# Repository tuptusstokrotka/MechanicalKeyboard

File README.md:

# PlusMinus 40

Inspired by [Mochi40](https://github.com/Aidan-OS/Mochi40), which already allows you to choose 1 out of 4 bottom row layout, but this wasn't enough for me. This is my first approach to 40% keyboards and with a changed bottom row to make it fit to my needs I gave it a go.

So I made this:

[Keyboard Layout Editor](http://www.keyboard-layout-editor.com/##@_name=PlusMinus%2040&author=Julian%3B&@_c=%23aaaaaa%20%3B&=0,0&_c=%23cccccc%20%3B&=0,1&=0,2&=0,3&=0,4&=0,5&=4,5&=4,4&=4,3&=4,2&=4,1&_c=%23777777%20&w:1.5%3B&=4,0%3B&@_w:1.25%3B&=1,0&_c=%23cccccc%20%3B&=1,1&=1,2&=1,3&=1,4&=1,5&=5,5&=5,4&=5,3&=5,2&=5,1&_c=%23aaaaaa%20&w:1.25%3B&=5,0%3B&@_c=%23777777%20&w:1.5%3B&=2,0&_c=%23cccccc%20%3B&=2,1&=2,2&=2,3&=2,4&=2,5&=6,5&=6,4&=6,3&=6,2&=6,1&=6,0%3B&@_y:-0.5&x:12.75&c=%23aaaaaa%20%3B&=7,0%0A%0A%0A%0A%0A%0A%0A%0A%0Ae0%3B&@_y:-0.5&c=%23777777%20&w:1.25%3B&=3,0&_w:1.25%3B&=3,1&_w:1.25%3B&=3,2&_c=%23aaaaaa%20&w:2.25%3B&=3,4&_w:2.75%3B&=7,5&_c=%23777777%20&w:1.25%3B&=7,3&_w:1.25%3B&=7,2&_w:1.25%3B&=7,1)

The files needed for https://jlcpcb.com are located in the production folder:

* `pcb/production`

Once `pcb.zip` has been uploaded, you can continue with the selected default options. You can optionally change the solder mask color, which changes the final color of your PCB.

When using their assembly service, you will need to upload the following files separately:

* `bom.csv`
* `positions.csv`

These files were all generated with Fabrication Toolkit for KiCad: https://github.com/bennymeg/Fabrication-Toolkit

## Acrylic Case

Case files are in the `DXF` folder.

#### note It is nessessary to add at least 2 stanoffs in the middle of a keyboard, due to the bending
---

### Parts List
| Description | Qty | Notes |
| ----------- | --- | ----- |
| 3mm acrylic | 7 | Qty = number of case layers
| 1.5mm acrylic | 1 | Switch plate
| M3x20mm chicago bolt | 6 | [Link](https://www.aliexpress.us/item/2251832451307213.html)
| M3x10mm chicago bolt | 1 | [Link](https://www.aliexpress.us/item/2251832451307213.html)
| M3x6mm screw | 1 - 6 | [Link](https://www.aliexpress.us/item/2255800885711092.html)
| M2x4mm round standoff | 7 | [Link](https://www.aliexpress.us/item/2251832782591461.html)
| M2x3mm screw | 7 | [Link](https://www.aliexpress.us/item/2255800480170108.html)
| M2x4mm screw | 7 | [Link](https://www.aliexpress.us/item/2255800480170108.html)
| 1mm EVA foam | 1 | Case foam
| 1.5mm EVA foam | 1 | Switch plate foam, [link](https://www.aliexpress.us/item/3256804208838525.html)
| 2mm EVA foam | 1 | Switch plate foam
| MX Switch | 38 - 44 |
| Adhesive rubber feet | 4

Keycap sizes will depend on the layout you're building (refer to KLE layout above).  Blank uniform-profile keycaps works really great for this keyboard since the keys have a vertical orientation.  I found my blank XDA PBT keycaps on AliExpress.  The specific ones I use in my build were purchased [here (1u - 2u)](https://www.aliexpress.us/item/3256804203440964.html) and [here (3u)](https://www.aliexpress.us/item/3256801190573750.html).

| Keycap | Qty |
| ------ | --- |
| 1u | 18 - 28
| 1.25u | 8
| 1.5u | 4
| 1.75u | 4
| 2u | 0 - 4
| 3u | 0 - 2

### Assembly

The M3 hardware is for the keyboard case.  The shorter M3 fastener goes above the USB connector.  You will need to use a wafer head (flat) screw on the bottom to keep the port clear for the USB cable.  You can optionally use the same M3x6mm wafer head screws for the entire bottom of the case instad of the chicago bolt ones, which is what I did for my build.

The M2 hardware is to fasten the PCB to the case.  The M2x3mm screws go on the bottom, and the M2x4mm screws go on the top (PCB side), with the M2x4mm standoff extending through the bottom of the case.  The PCB is essentially floating vertically, but is held up by the 1mm case foam.  Below is simple diagram of how everything fits together.

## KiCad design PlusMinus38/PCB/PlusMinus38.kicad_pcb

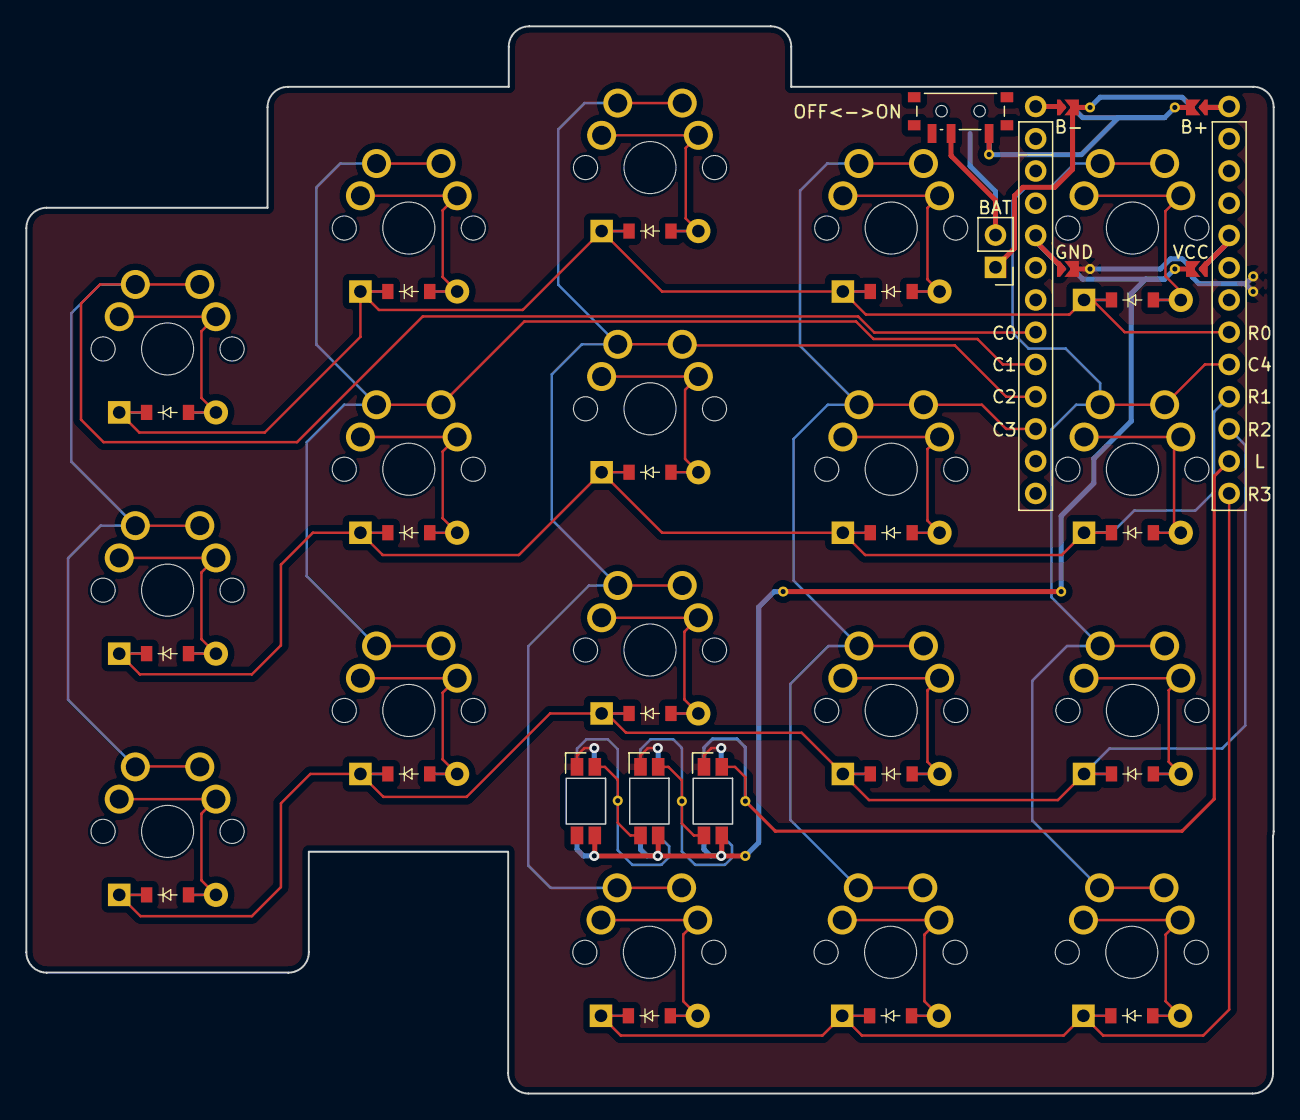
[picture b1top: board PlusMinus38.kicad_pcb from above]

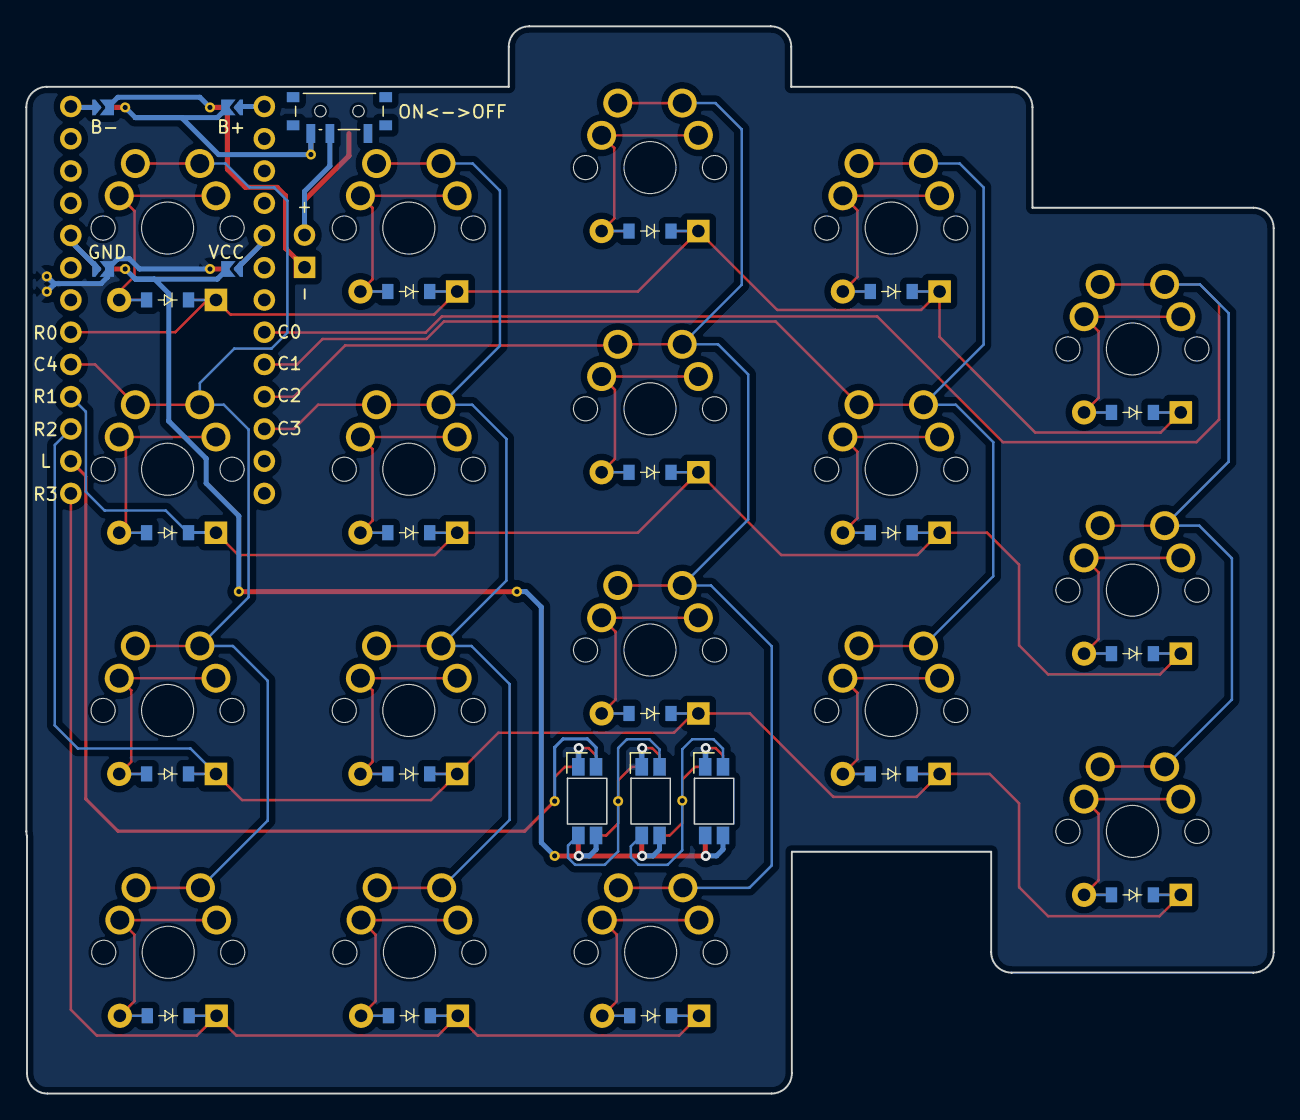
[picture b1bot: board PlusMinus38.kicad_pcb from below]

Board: 2 copper layers, 98.2 x 84.1 mm, 42 parts (20 on the bottom side), 34 nets.

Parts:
BAT: PinHeader_1x02_P2.54mm_Vertical
D1, D2, D3, D4, D5, D6, D7, D8, D9, D10, D11, D12, D13, D14, D15, D16, D17, D18: ComboDiode
LED1, LED1#2, LED1#3: led_SK6812mini-e (per-key, reversible)
MCU1: mcu_supermini_nrf52840
PWR1: power_switch_smd_side
S1, S2, S3, S4, S5, S6, S7, S8, S9, S10, S11, S12, S13, S14, S15, S16, S17, S18: switch_mx

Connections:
B+: PWR1.1, PWR1.3
C0: MCU1.18, S1.1, S2.1, S3.1
C1: MCU1.17, S4.1, S5.1, S6.1
C2: MCU1.16, S7.1, S8.1, S9.1, S16.1
C3: MCU1.15, S10.1, S11.1, S12.1, S17.1
C4: MCU1.8, S13.1, S14.1, S15.1, S18.1
GND: LED1.3, LED1#2.3, LED1#3.3
LED_0_IN: LED1#3.4, MCU1.11
LED_0_OUT: LED1#2.4, LED1#3.2
LED_1_OUT: LED1.4, LED1#2.2
PWR+: BAT.2, PWR1.2
R0: D3.1, D6.1, D9.1, D12.1, D15.1, MCU1.7
R1: D2.1, D5.1, D8.1, D11.1, D14.1, MCU1.9
R2: D1.1, D4.1, D7.1, D10.1, D13.1, MCU1.10
R3: D16.1, D17.1, D18.1, MCU1.12
VCC: LED1.1, LED1#2.1, LED1#3.1
index_bottom: D10.2, S10.2
index_home: D11.2, S11.2
index_top: D12.2, S12.2
inner_bottom: D13.2, S13.2
inner_home: D14.2, S14.2
inner_top: D15.2, S15.2
middle_bottom: D7.2, S7.2
middle_home: D8.2, S8.2
middle_top: D9.2, S9.2
pinky_bottom: D1.2, S1.2
pinky_home: D2.2, S2.2
pinky_top: D3.2, S3.2
ring_bottom: D4.2, S4.2
ring_home: D5.2, S5.2
ring_top: D6.2, S6.2
thumb_1_home: D16.2, S16.2
thumb_2_home: D17.2, S17.2
thumb_3_home: D18.2, S18.2

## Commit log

2024-04-25 handwired keyboard
2024-06-14 Organised qmk keymap files
2024-06-14 whoops
2024-06-16 Separated default from Luna keymap
2024-06-23 Added ortho30 directory and via.json
2024-06-29 Added basic 30 keyboard - experimenta
2024-06-29 Small fixes
2024-07-08 Added 40% gerbers
2024-07-12 Added Colmak-DH layout
2024-07-17 fixinig naming issues and minor colemak inconvenience
2024-07-17 Added 30% pictures
2024-08-18 Reorganise files, Added 34keys
2024-08-18 Unified naming across all keyboards
2024-08-20 Removed homerow from secondary layers. Final touch with 34.
2024-08-20 spacing
2024-11-14 Added graphical representation, fixed naming, Added new layout, new keymap
2024-11-14 Adding new design split 37
2024-12-25 added dxf for 37 keys
2025-05-03 Added 5% macropad template
2025-05-04 Modifed 5% keymap, added most used hotkeys
2025-08-19 Added PCB for split +-38
2025-08-19 Added solderjumpers to reverse the keyboard
2025-08-20 Fixed reverse solder pads traces. Updated ergogen yaml to match pcb
2025-08-20 Added power switch
2025-08-20 Added leds to the rgb chain
2025-08-20 Fliped the solder jumpers for better access
2025-09-21 Fixed power line trace width
2025-09-21 Update the ergogen yaml to the latest config
